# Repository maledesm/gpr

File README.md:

# GPR FMCW — Tesis

Radar de penetración terrestre de onda continua modulada en frecuencia.
Firmware de adquisición sobre ESP32-C3 + PCM1808, y procesamiento en Python.

**Facultad de Ingeniería, UBA.**

---

## Empezar por acá

| Quiero… | Voy a |
|---|---|
| **Medir ahora** | doble click en **`medir.bat`** → graba a CSV y abre el gráfico en vivo |
| **Ver una captura vieja** | doble click en **`graficar.bat`** (o arrastrarle un `.csv` encima) |
| **Ver si el software está sano** | doble click en **`pruebas.bat`** — corre sin hardware |
| **Cargar el firmware** | `firmware/PCM1808_ESP32C3/` ← **el único vigente** |
| **Cablear la placa** | [`docs/conexionado.md`](docs/conexionado.md) |
| **Caracterizar el sampler** | [`docs/validacion_banco.md`](docs/validacion_banco.md) |
| **Entender el circuito** | [`docs/PCM1808_hardware.md`](docs/PCM1808_hardware.md) |
| **Usar los comandos del firmware** | [`docs/PCM1808_uso.md`](docs/PCM1808_uso.md) |

Los `.bat` no llevan rutas fijas: se ubican solos con `%~dp0`, así que el repo
se puede mover, renombrar o clonar en otra máquina y siguen andando.

Si preferís la consola, es lo mismo:

```powershell
& "$env:USERPROFILE\venvs\gpr-win\Scripts\python.exe" .\adquisicion\medir.py
```

> **Antes de medir**: el ESP32 enchufado y el **Monitor Serie del Arduino IDE
> cerrado**. Un solo programa puede tener el puerto abierto.

---

## Parámetros del radar

| | |
|---|---|
| Banda de diseño | **1,0 – 2,0 GHz** |
| Ancho de banda | 1000 MHz |
| Resolución en distancia | 15 cm en aire · 5 cm en suelo (εr ≈ 9) |
| Digitalización | PCM1808, 24 bit, 8–96 kHz |
| Controlador | ESP32-C3 SuperMini |

```
f_beat = 2·R·BW / (c·T_sweep) = (6,67 / T_sweep) Hz por metro
```

**Lo que entrega el VCO hoy**, con la tabla de predistorsión actual (rango del
DAC de 0 a 3,00 V): **943 – 1982 MHz**, o sea BW 1039 MHz y 14,4 cm de
resolución. Cubre prácticamente la banda de diseño y con algo más de ancho.

Para llegar a **2,000 GHz exactos harían falta 3,091 V**, por encima del tope de
3,00 V que tiene hoy la tabla. Es alcanzable —el DAC llega hasta VDD = 3,3 V—
pero implica regenerar `tabla_vco.h` con otro `V_MAX_USO`. Los 3,00 V son un
margen elegido, no un límite del hardware. Medición y análisis en
[`VCO/analisis_vco.py`](VCO/analisis_vco.py).

---

## Estructura

```
firmware/
  PCM1808_ESP32C3/      ★ EL FIRMWARE ACTUAL. Es el que va en la placa.
                          Salida en texto (Serial Plotter, Telemetry Viewer)
                          y en binario con CRC para el software de Python.
  prueba_mcp4725/         Rampa de sintonía del VCO por I²C. Sketch AISLADO:
                          no toca el I²S ni el PCM1808, para probar el DAC sin
                          arriesgar la cadena de adquisición.
    tabla_vco.h           GENERADO por VCO/analisis_vco.py — no editar a mano.
  generador_patron/       Arduino Uno: cuadrada de 100 Hz como señal de
                          referencia, para validar sin el radar.
  historico/              Etapas viejas. NO cargar: ver su README.

adquisicion/            Software de captura y visualización (corre en WINDOWS)
  medir.py                Lanzador: arranca los dos de abajo.
  grabarserial.py         Graba el flujo binario a CSV, con metadata completa.
  graficarserial.py       Espectro + osciloscopio + B-scan en tiempo real.
  protocolo.py            Decodificador de tramas.   Autoprueba: --test
  dsp.py                  Ventanas, FFT, filtros, distancia.  Autoprueba: --test

adquisicion_audio/      Captura por placa de sonido (U-Phoria UMC22), TEMPORAL
  medir_audio.py          Lanzador: grabador + el MISMO graficarserial.py.
  grabaraudio.py          Graba a CSV (igual formato) + WAV crudo de 2 canales.
                          Autoprueba: --test.  Utilidades: --listar, --calibrar
  audio.py                Dispositivos, API de audio, WAV.  Autoprueba: --test
                          Ver su README: el corte de 10 Hz de la placa es MAS
                          alto que el del PCM1808, no mas bajo.

docs/
  conexionado.md          Cableado, alimentación, divisores. Empezar por acá.
  validacion_banco.md     Caracterización con generador de funciones.
  PCM1808_hardware.md     Estudio de circuito: relojes, pasa-altos, ruido.
  PCM1808_uso.md          Comandos del firmware y resolución de problemas.
  placa_audio_umc22.md    Puesta en marcha de la UMC22 en una máquina nueva.

analisis/               Procesamiento offline (corre en WSL o en Windows)
  v1/  Espectros y señales crudas por medición.
  v2/  Segmentación por sweeps + espectro promediado vs. distancia.

VCO/                    Caracterización y linealización del barrido
  Caracteristica VCO.csv  34 puntos medidos cada 100 mV. Decimales con COMA.
  analisis_vco.py         Genera firmware/prueba_mcp4725/tabla_vco.h + curva_vco.png
                          ⚠ tabla_vco.h está DUPLICADA (prueba_mcp4725 y
                          gpr_barrido) y el script escribe solo la primera. Si la
                          regenerás, copiala a mano a la otra. Pendiente:
                          que el script escriba las dos.
  grafico_vco.py          Figura F vs V con la sensibilidad dF/dV.
  grafico_capturas_dac.py Figura de las 4 capturas de osciloscopio de la rampa.
  Osciloscopio DAC/       Capturas SDS00001..4 (.CSV y .BMP).

Filtro Pasabajos/       Caracterización de un filtro activo. Trabajo aparte del
                        radar, se dejó acá para no perderlo.

simulacion/
  beat_simulado.py        Genera un WAV con la señal de beat de varios blancos,
                          para reproducir por la placa de sonido y validar todo
                          el procesamiento sin tener el radar.
  lpda_meep.py            Antena log-periódica en MEEP.

datos/                  Capturas. Las del ESP32 se llaman AAAA-MM-DD_HHMMSS.csv;
                        las SDS*.CSV son del osciloscopio Siglent.
```

> **Nota**: los CSV de `datos/` están en `.gitignore` porque se generan en cada
> medición. Para conservar una: `git add -f datos/2026-08-15_143000.csv`

---

## Los dos entornos de Python

Son distintos a propósito y no comparten scripts:

| | Dónde | Para qué |
|---|---|---|
| `C:\Users\tinch\venvs\gpr-win` | **Windows** | Adquisición. Obligatorio: el ESP32 es un puerto COM y **WSL 2 no lo ve** |
| `~/MEDI/venv_gpr` | WSL | Análisis offline. No toca hardware |

Detalles del entorno de Windows —incluido el workaround del certificado de
Kaspersky que rompe `pip`— en [`adquisicion/README.md`](adquisicion/README.md).

---

## Estado

Funcionando y verificado sobre hardware:

- [x] Digitalización con PCM1808, validada contra generador de funciones
- [x] Frecuencia de muestreo variable en caliente (8–96 kHz)
- [x] Enlace binario con CRC: 8001,6 S/s medidos contra 8000 nominales, cero pérdidas
- [x] Grabación a CSV con metadata y verificación de continuidad
- [x] Visualización en vivo: espectro, osciloscopio y B-scan
- [x] Procesamiento FMCW de las capturas de osciloscopio

Pendiente, en orden de importancia:

- [ ] **Acelerar el sweep FMCW.** Es el bloqueante principal. Con el
      `T_sweep ≈ 1,46 s` actual, las frecuencias de beat de la zona útil
      (0,2–2 m) caen entre 0,9 y 9 Hz, o sea **adentro del pasa-altos del
      PCM1808**, que no se puede desactivar. Bajando a 5–10 ms el beat pasa a
      130 Hz – 2,7 kHz y el problema desaparece. Números en
      [`docs/PCM1808_hardware.md`](docs/PCM1808_hardware.md) §0.
- [ ] **Sincronismo con el sweep.** Sin él no se puede promediar
      coherentemente. Tres arquitecturas evaluadas en §6 del mismo documento.
- [ ] Caracterizar el piso de ruido con batería. Una captura preliminar dio
      ~62 dB de SNR (≈10 bits efectivos) con un pico de red en 50 Hz, bastante
      por debajo de los 99 dB del chip.
- [ ] Atenuador de entrada, dimensionado para 3 Vpp (el peor caso).
- [ ] Segundo canal para I/Q.

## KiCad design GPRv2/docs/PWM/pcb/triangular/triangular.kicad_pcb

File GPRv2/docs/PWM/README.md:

# Generador de triangular (reemplazo del SDG830)

Schmitt + integrador que barre el VCO: triangular de ~0 a 3 V (medida 0,36–3,36 V)
de 20 a 275 ms de período, con la cuadrada como sync hacia GPIO10 del ESP32-C3.
Hoy está armado con **LM324** (680k ∥ R5 y 2 × 680k ∥ R2) a 12 V.

```
PWM/
  simulacion/   LTspice: circuitos, modelos y figuras
  pcb/          proyecto KiCad 10 de la placa
  mediciones/   capturas del osciloscopio y del analizador de espectro, con sus análisis
```

Python: `C:\Users\tinch\venvs\gpr-win\Scripts\python.exe`. LTspice 24:
`C:\Program Files\LTC\LTspice.exe`.

## `simulacion/`

**Los modelos están al lado de los `.asc` a propósito**: los símbolos (`.asy`) traen
su `SpiceModel` sin ruta y LTspice los busca en la carpeta del circuito. No moverlos.

| circuito | qué es |
|---|---|
| `PWM.asc` | el PWM original de Circuitos II (~135 kHz), base del resto |
| `triangular.asc` | paso 1: Schmitt TL072 + integrador llevado a ~10 Hz |
| `triangular2.asc` | paso 2: restador a 0–3 V y buffer del sync (UniversalOpAmp2) |
| `triangular3.asc` | paso 3: con TLC2272 real y zener 1N4729A en la salida |
| `triangular3_LM324.asc` | lo que está armado: LM324 con los paralelos de R5 y R2 |

| modelo | |
|---|---|
| `TLC2272.lib/.asy`, `TLC2262.lib/.asy`, `TL072.sub/.asy`, `LM324.sub/.asy` | operacionales |
| `zener_1N472xA.lib`, `1N4729A.asy` | zeners de Diodes Inc. |

Scripts: `graficar_triangular2.py` y `graficar_triangular3.py` leen el `.raw` y arman la
figura del paso. `zener.bat` corre `simular_zener.py` (variantes del netlist de la placa,
a `zener/`), `graficar_zener.py` y `tolerancias.py`. `ruido_opamp.py` compara el ruido de
los modelos.

Para simular en batch sin que se cuelgue: `LTspice.exe -netlist x.asc` y después
`LTspice.exe -b x.net`.

## `pcb/`

Abrir `triangular.kicad_pro`. Las huellas propias (llave, puente de cable) están en
`triangular.pretty/`, que el `fp-lib-table` busca con `${KIPRJMOD}`: tiene que quedar al
lado del proyecto. Verificado con `kicad-cli`: ERC sin errores, DRC sin pads sin conectar
y sin diferencias con el esquemático (queda solo un aviso de que RV1 no coincide con la
huella de la biblioteca, que ya estaba).

`simular_kicad.bat` exporta el netlist del esquemático y lo simula en LTspice
(`triangular_kicad.cir`, con los modelos de `../simulacion/`). Es la base de
`simulacion/simular_zener.py`.

## `mediciones/`

| carpeta | qué hay |
|---|---|
| `2026-11-02_tanda1/` | osciloscopio, 20 / 100 / 275 ms, pocos períodos por captura |
| `2026-11-02_tanda2/` | osciloscopio, 20 / 101 / 273 ms, más períodos (81 / 15 / 30) |
| `2026-11-02_vco_maxhold/` | salida del VCO en el SSA3032X, Max Hold de 0,8 a 3 GHz |
| `2026-11-06-tektronix_triangular/` | Tektronix TBS1102B a 0,5 V/div: 20, 100 y 273 ms. La medición buena de la triangular |
| `2026-11-06-siglent_vco+triangular/` | zero span del VCO cada 25 MHz (995 a 1995 MHz), disparado por el sync, más un Max Hold |

- `analizar_tektronix.py [carpeta]` — una figura por captura del Tek (`ALL000x_analisis.png`).
- `analizar_zerospan.py [carpeta]` — f(t), df/dt, f(V) contra la curva estática y desvío de
  una recta; los puntos medidos quedan en `zerospan_puntos.csv` (base del mapa θ).

**Resultados del 2026-11-06:** triangular de 0,12 a 3,06 V con no linealidad de 0,1–0,3 %
(el ~1 % y el escalón de 0,95 V que mostraba el Siglent eran del osciloscopio), subida y
bajada con ~3 % de diferencia de pendiente. El VCO barre **985 a 1999 MHz** (1014 MHz),
la subida dura 50,5 ms y la bajada 49,4 ms, df/dt va de ~14 a ~27 MHz/ms y f(t) se aparta
hasta ~78 MHz de una recta.

- `analizar_mediciones.py [carpeta]` — período, ciclo útil, linealidad, espectro contra una
  triangular ideal y huecos en el registro. Cada carpeta tiene su asignación
  archivo → posición del pote en `CARPETAS`, adentro del script. Escribe las figuras y
  `mediciones_triangular.json` en la carpeta de la tanda.
- `analizar_vco_maxhold.py [carpeta]` — banda que barre el VCO y su 2º armónico.

**Lo que conviene saber de las capturas:**

- Las dos tandas están a **1 V/div**: el escalón del osciloscopio es de 40 mV. Para la
  próxima, 0,5 V/div con −1,7 V de offset.
- Las "conmutaciones antes de tiempo" que se veían con el pote al máximo **eran huecos en
  el registro del osciloscopio**, no el generador: la triangular sigue como si se hubiera
  cortado un pedazo de señal y los flancos siguientes llegan adelantados justo ese tiempo
  (49 ms medidos contra 52 predichos, 15,2 contra 15,7). Aparecen a 100 ms/div y más
  lento; a 50 ms/div o más rápido, ninguno. La figura es `huecos_registro.png`.
- La triangular de la tanda 2 está ~0,15 V más alta que la de la tanda 1. Se usa así y se
  corrige en el código.
- **Armónicos del VCO**: ver la sección "Pendiente: armónicos del VCO" en `GPRv2/CLAUDE.md`.

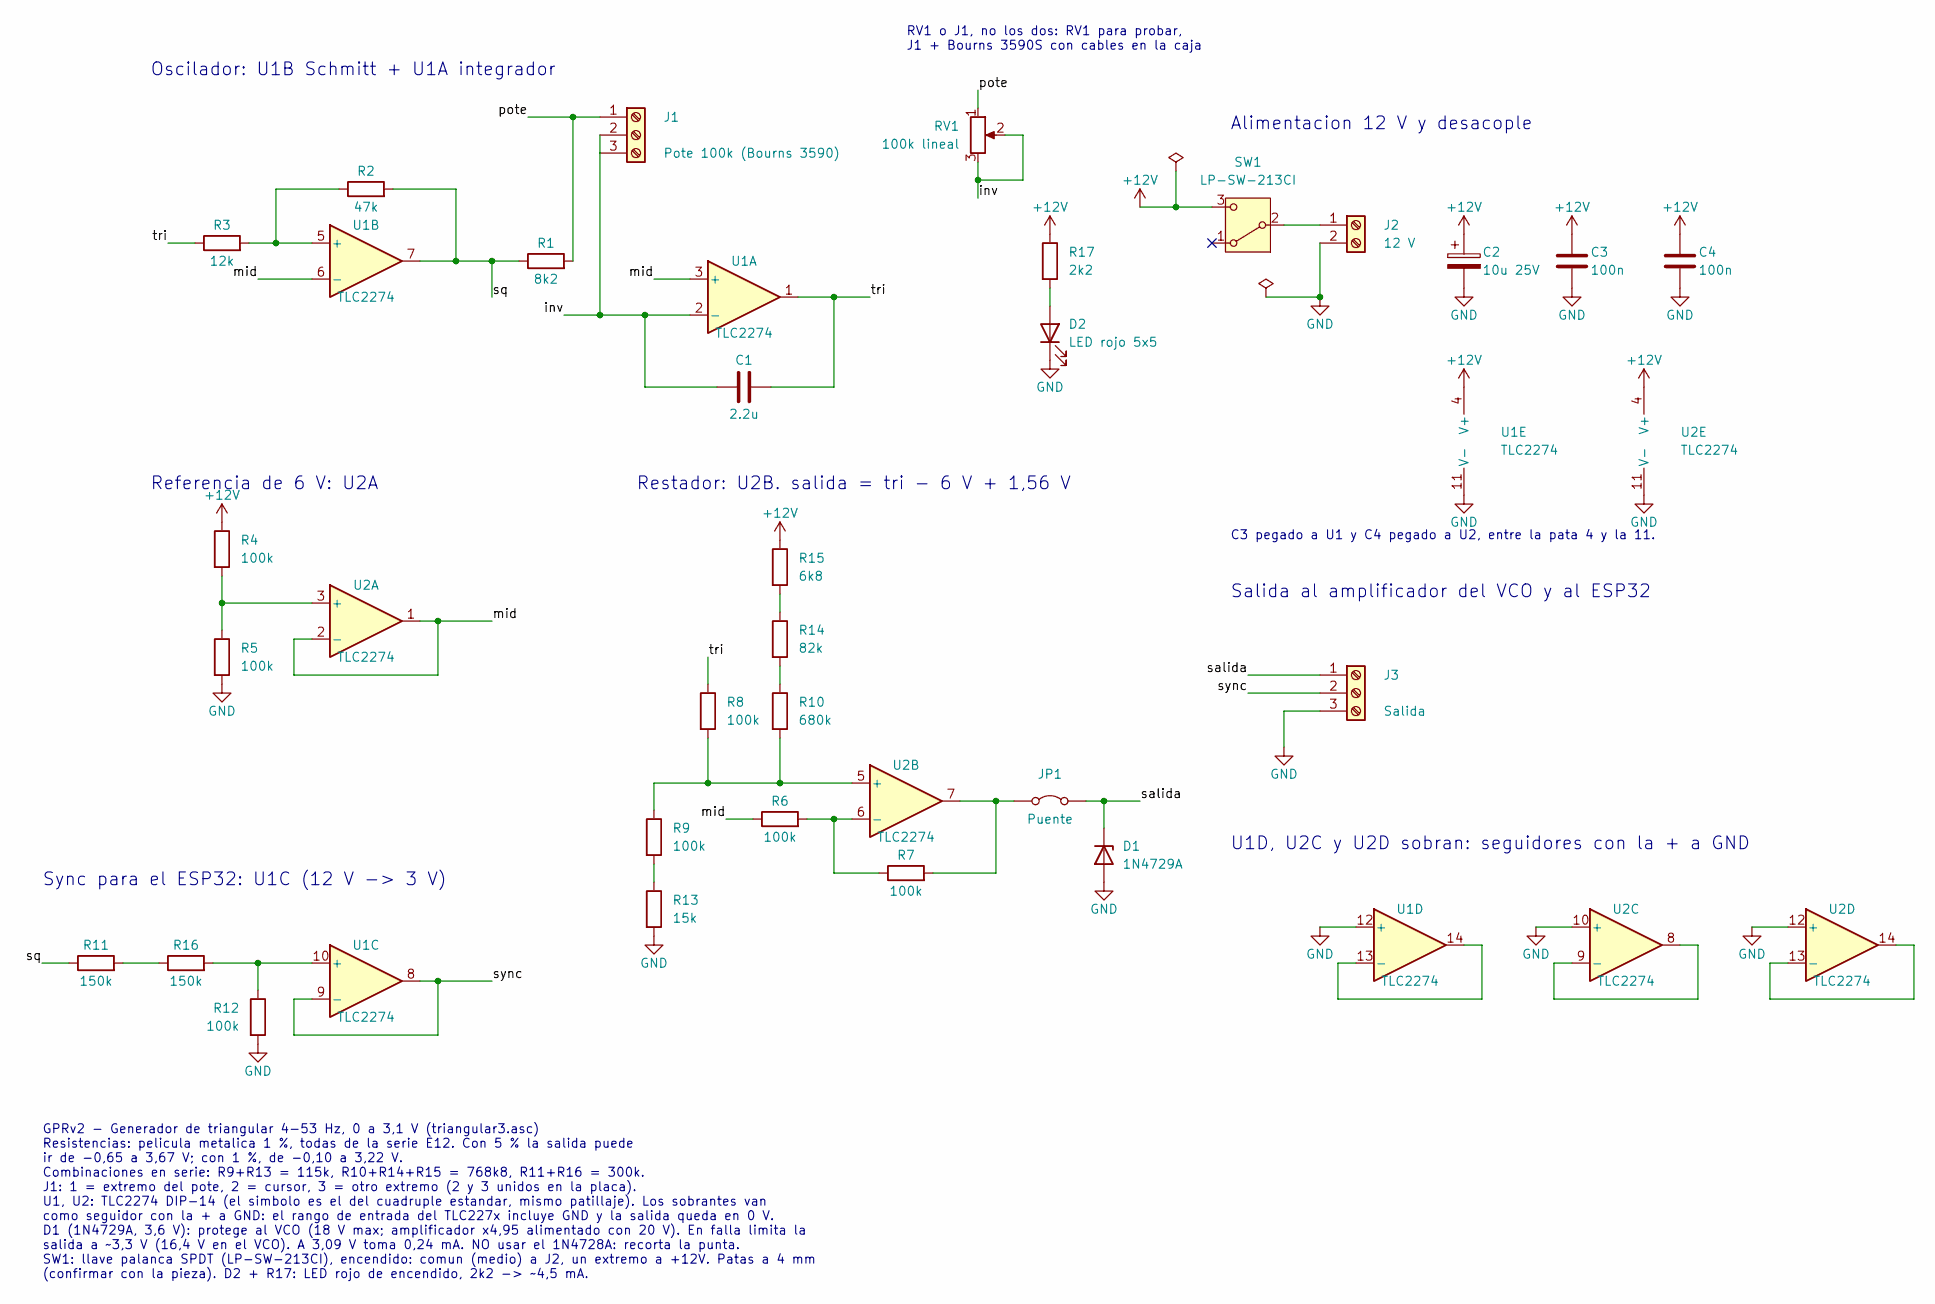
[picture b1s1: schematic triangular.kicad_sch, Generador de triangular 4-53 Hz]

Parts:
C1: 2.2u; C_Rect_L18.0mm_W9.0mm_P15.00mm_FKS3_FKP3
C2: 10u 25V; CP_Radial_D5.0mm_P2.00mm
C3, C4: 100n; C_Disc_D5.0mm_W2.5mm_P5.00mm
D1: 1N4729A; D_DO-41_SOD81_P10.16mm_Horizontal
D2: LED rojo 5x5; LED_Rectangular_W5.0mm_H5.0mm
J1: Pote 100k (Bourns 3590); TerminalBlock_Phoenix_MKDS-1,5-3_1x03_P5.00mm_Horizontal
J2: 12 V; TerminalBlock_Phoenix_MKDS-1,5-2_1x02_P5.00mm_Horizontal
J3: Salida; TerminalBlock_Phoenix_MKDS-1,5-3_1x03_P5.00mm_Horizontal
JP1: Puente; Puente_Cable_P22.5mm
R1: 8k2; R_Axial_DIN0207_L6.3mm_D2.5mm_P10.16mm_Horizontal
R2: 47k; R_Axial_DIN0207_L6.3mm_D2.5mm_P10.16mm_Horizontal
R3: 12k; R_Axial_DIN0207_L6.3mm_D2.5mm_P10.16mm_Horizontal
R4, R5, R6, R7, R8, R9, R12: 100k; R_Axial_DIN0207_L6.3mm_D2.5mm_P10.16mm_Horizontal
R10: 680k; R_Axial_DIN0207_L6.3mm_D2.5mm_P10.16mm_Horizontal
R11, R16: 150k; R_Axial_DIN0207_L6.3mm_D2.5mm_P10.16mm_Horizontal
R13: 15k; R_Axial_DIN0207_L6.3mm_D2.5mm_P10.16mm_Horizontal
R14: 82k; R_Axial_DIN0207_L6.3mm_D2.5mm_P10.16mm_Horizontal
R15: 6k8; R_Axial_DIN0207_L6.3mm_D2.5mm_P10.16mm_Horizontal
R17: 2k2; R_Axial_DIN0207_L6.3mm_D2.5mm_P10.16mm_Horizontal
RV1: 100k lineal; Potentiometer_Alps_RK163_Single_Horizontal
SW1: LP-SW-213CI; SW_Palanca_SPDT_P4mm
U1, U2: TLC2274; DIP-14_W7.62mm_Socket

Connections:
+12V: C2.1, C3.1, C4.1, R4.1, R15.1, R17.1, SW1.3 (C), U1.4 (V+), U2.4 (V+)
/inv: C1.1, J1.2, J1.3, RV1.2, RV1.3, U1.2 (-)
/mid: R6.1, U1.3 (+), U1.6 (-), U2.1, U2.2 (-)
/pote: J1.1, R1.2, RV1.1
/salida: D1.1 (K), J3.1, JP1.2 (B)
/sq: R1.1, R2.2, R11.1, U1.7
/sync: J3.2, U1.8, U1.9 (-)
/tri: C1.2, R3.1, R8.1, U1.1
GND: C2.2, C3.2, C4.2, D1.2 (A), D2.1 (K), J2.2, J3.3, R5.2, R12.2, R13.2, U1.11 (V-), U1.12 (+), U2.10 (+), U2.11 (V-), U2.12 (+)
unnamed: D2.2 (A), R17.2
unnamed: J2.1, SW1.2 (B)
unnamed: JP1.1 (A), R7.2, U2.7
unnamed: R10.1, R14.2
unnamed: R11.2, R16.1
unnamed: R9.2, R13.1
unnamed: R14.1, R15.2
unnamed: R2.1, R3.2, U1.5 (+)
unnamed: R12.1, R16.2, U1.10 (+)
unnamed: U1.13 (-), U1.14
unnamed: R4.2, R5.1, U2.3 (+)
unnamed: R8.2, R9.1, R10.2, U2.5 (+)
unnamed: R6.2, R7.1, U2.6 (-)
unnamed: U2.8, U2.9 (-)
unnamed: U2.13 (-), U2.14

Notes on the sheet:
Oscilador: U1B Schmitt + U1A integrador
RV1 o J1, no los dos: RV1 para probar, J1 + Bourns 3590S con cables en la caja
Referencia de 6 V: U2A
Restador: U2B. salida = tri - 6 V + 1,56 V
Sync para el ESP32: U1C (12 V -> 3 V)
Alimentacion 12 V y desacople
C3 pegado a U1 y C4 pegado a U2, entre la pata 4 y la 11.
Salida al amplificador del VCO y al ESP32
U1D, U2C y U2D sobran: seguidores con la + a GND
GPRv2 - Generador de triangular 4-53 Hz, 0 a 3,1 V (triangular3.asc) Resistencias: pelicula metalica 1 %, todas de la serie E12. Con 5 % la salida puede ir de -0,65 a 3,67 V; con 1 %, de -0,10 a 3,22 V. Combinaciones en serie: R9+R13 = 115k, R10+R14+R15 = 768k8, R11+R16 = 300k. J1: 1 = extremo del 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

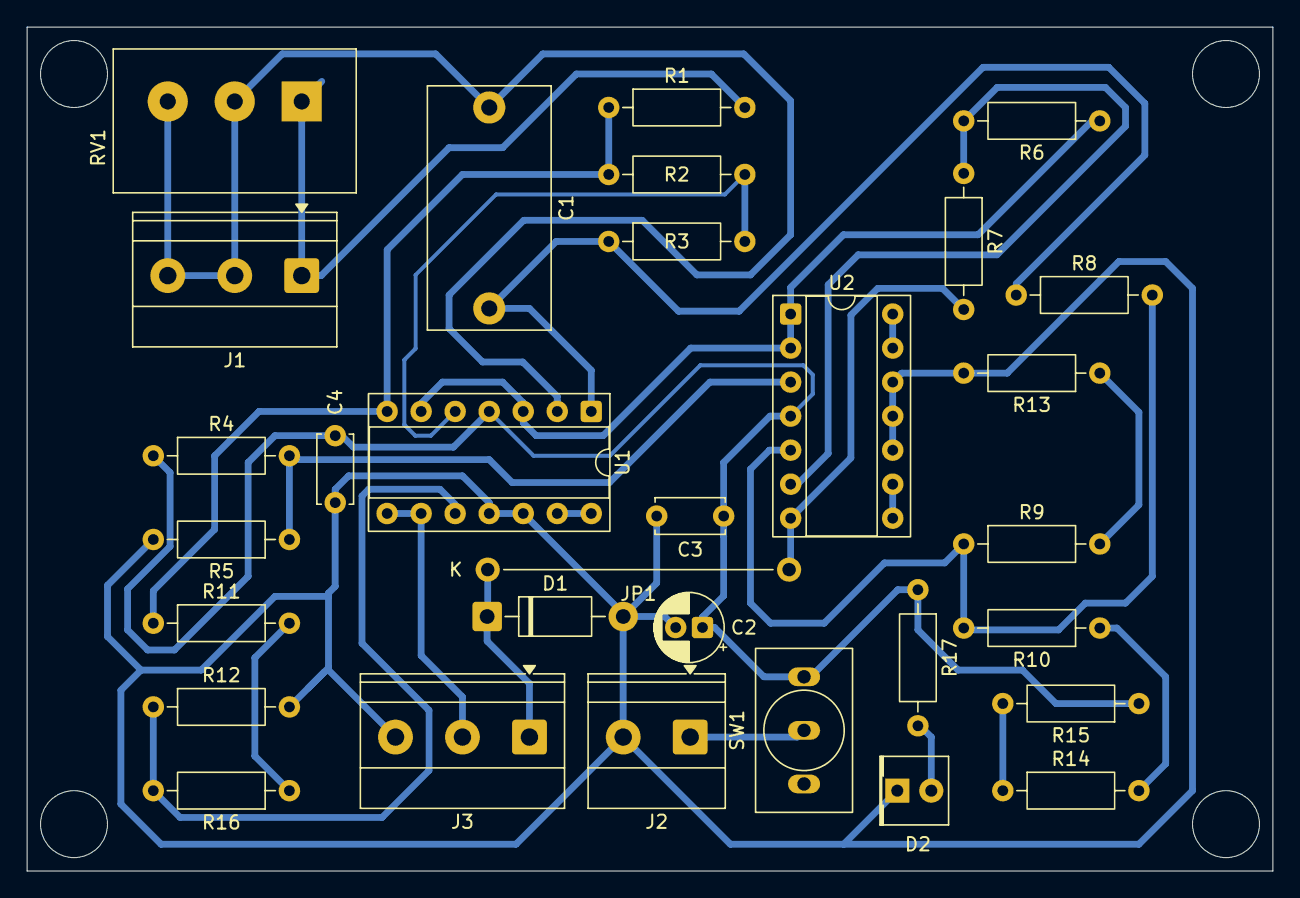
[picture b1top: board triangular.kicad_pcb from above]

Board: 2 copper layers, 93.0 x 63.0 mm, 31 parts (0 on the bottom side), 24 nets.

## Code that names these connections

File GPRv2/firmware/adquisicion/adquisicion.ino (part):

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//      fs 48000     la cambia (8000 a 96000)
//
//  Salida: "L,sync" por linea (CSV). L en cuentas del ADC (+-8388607);
//  sync = muestras transcurridas desde el ultimo flanco de subida en GPIO10,
//  o -1 si todavia no llego ninguno. Se ve como diente de sierra en el
//  plotter y da la fase dentro de la rampa en cada muestra.
//
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#define PIN_BCLK  5
#define PIN_LRCK  6
#define PIN_DIN   7
#define PIN_SYNC 10   // <- sync del generador, por divisor 10k/15k (3.00 V)
// <- triangular del generador, por divisor 4k7/4k7. Los 3 V se dividen a 1,5,
// que cae en el medio del rango util del ADC del C3 (~0 a 2,5 V con la
// atenuacion por defecto); a 3 V pelados el ADC se vuelve no lineal cerca del
// riel. El divisor tambien baja la impedancia de fuente a 2,35 kohm, que es
// lo que el ADC necesita ver para muestrear bien.
#define PIN_TRI   3

#define FS_DEF        48000   // uno de los "exactos" del PLL (16/32/48 kHz)
#define FS_MIN         8000   // minimo absoluto del PCM1808
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#define MAX_ETAPAS 5
static etapa_t  g_etapa[MAX_ETAPAS];
static uint8_t  g_n_etapas = 0;   // 0 = sin FIR, se usa el promedio de antes
static uint32_t g_retardo  = 0;   // retardo del filtro, en muestras de salida

// Empuja una muestra en una etapa. Devuelve true (y deja el resultado en *y)
// una vez cada dos.
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  // interno (~45k) queda en paralelo con la pata de abajo: con 10k/15k la
  // tension baja de 3,00 a 2,65 V, todavia sobre el umbral de 2,48 pero
  // justo. Si el sync aparece, mejor 10k/22k, que con el pulldown da 2,98 V.
  pinMode(PIN_SYNC, INPUT_PULLDOWN);
  attachInterrupt(PIN_SYNC, isrSync, RISING);
  analogReadResolution(12);   // la atenuacion queda en la maxima por defecto
  if (i2sArrancar(FS_DEF)) informar();
  Serial.println("# comandos: run | stop | fs [Hz]");
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  // ultima muestra del bloque, que es la que se le adjudica. Emitirla antes
  // de leerla costaria el tiempo de escribir el bloque entero por USB, que
  // son ~1 ms, o sea un 3% del periodo de la triangular.
  int tri = analogRead(PIN_TRI);
  // EXPERIMENTO 2026-09-18 (ver GPRv2/CLAUDE.md, "la triangular sale con dos
  // lineas"): la lectura cae al azar en uno de dos estados separados ~390
  // cuentas. Para saber si el estado cambia entre CONVERSIONES (el ADC o su
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  // lee dos veces mas, pegadas, y se emite todo en una linea "#v3,..." aparte
  // al final del bloque. Ningun script de la PC la mira: empieza con '#' y no
  // con "#v,". Sacar cuando el experimento termine.
  int tri2 = analogRead(PIN_TRI);
  int tri3 = analogRead(PIN_TRI);
  int64_t t_lect = esp_timer_get_time();

  // Copia del anillo. Si el indice no cambio entre antes y despues, no entro
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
